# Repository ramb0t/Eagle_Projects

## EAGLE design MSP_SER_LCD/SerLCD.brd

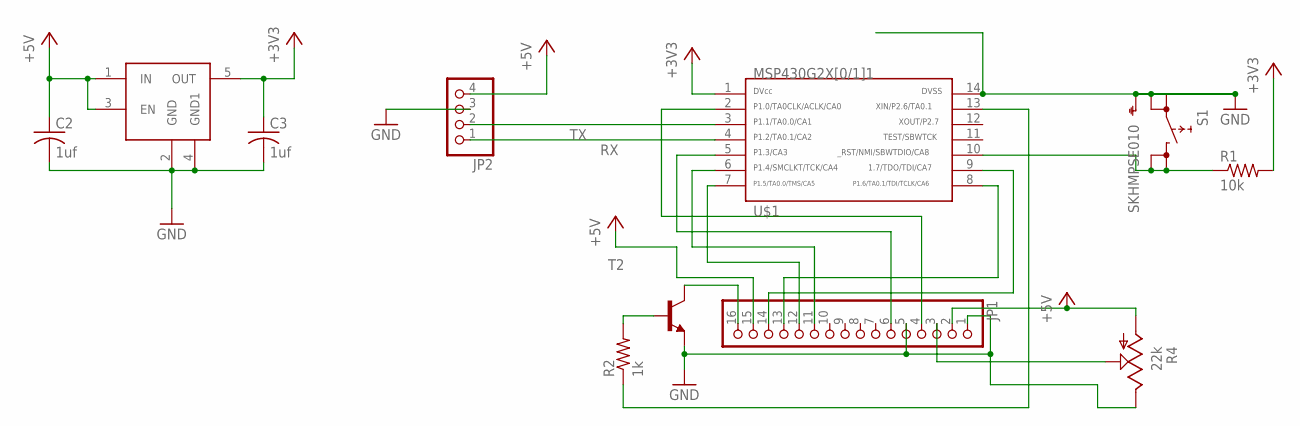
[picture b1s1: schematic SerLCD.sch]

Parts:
C2, C3: 1uf; C025-025X050
JP1: PINHD-1X16; 1X16
JP2: PINHD-1X4; 1X04
R1: 10k; 0207/10
R2: 1k; 0207/10
R4: 22k; CA6H
S1: SKHMPSE010; SKHMPXE010
T2: -NPN-TO92-EBC; TO92-EBC
U$1: G2X[0/1]1---N14; N14
U$2: TPS783XX; DBV-R-PDSO-G5

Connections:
+3V3: C3.1, R1.2, U$1.1, U$2.5 (OUT)
+5V: C2.1, JP1.2, JP1.15, JP2.4, R4.A, U$2.1 (IN), U$2.3 (EN)
GND: C2.2, C3.2, JP1.1, JP1.5, JP2.3, R4.E, S1.1 (1.1), S1.2 (1.2), S1.5 (SH), T2.E, U$1.14, U$2.2 (GND), U$2.4 (GND1)
unnamed: JP1.4, U$1.2
unnamed: JP1.6, U$1.5
unnamed: JP1.11, U$1.6
unnamed: JP1.12, U$1.7
unnamed: JP1.13, U$1.8
unnamed: JP1.14, U$1.9
unnamed: R1.1, S1.3 (2.1), S1.4 (2.2), U$1.10
unnamed: JP1.16, T2.C
unnamed: R2.2, T2.B
unnamed: R2.1, U$1.13
unnamed: JP1.3, R4.S
RX: JP2.1, U$1.4
TX: JP2.2, U$1.3

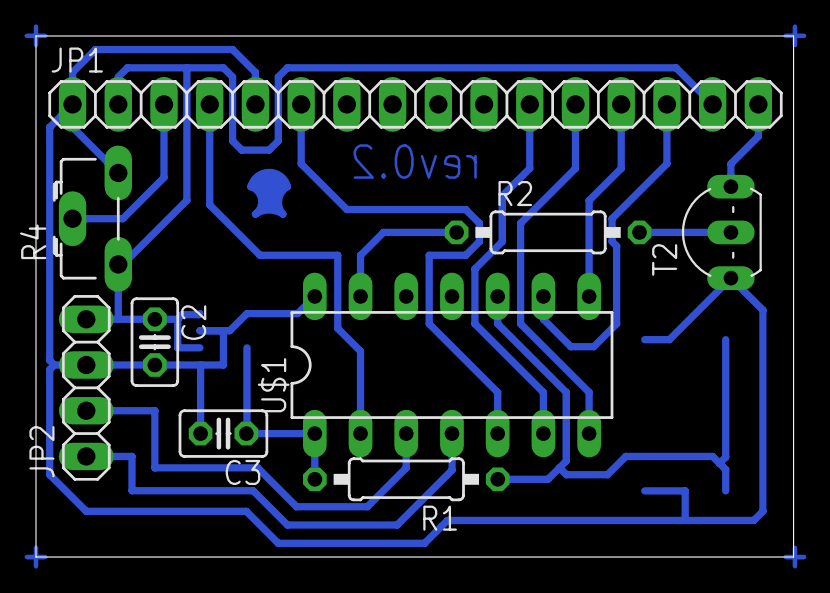
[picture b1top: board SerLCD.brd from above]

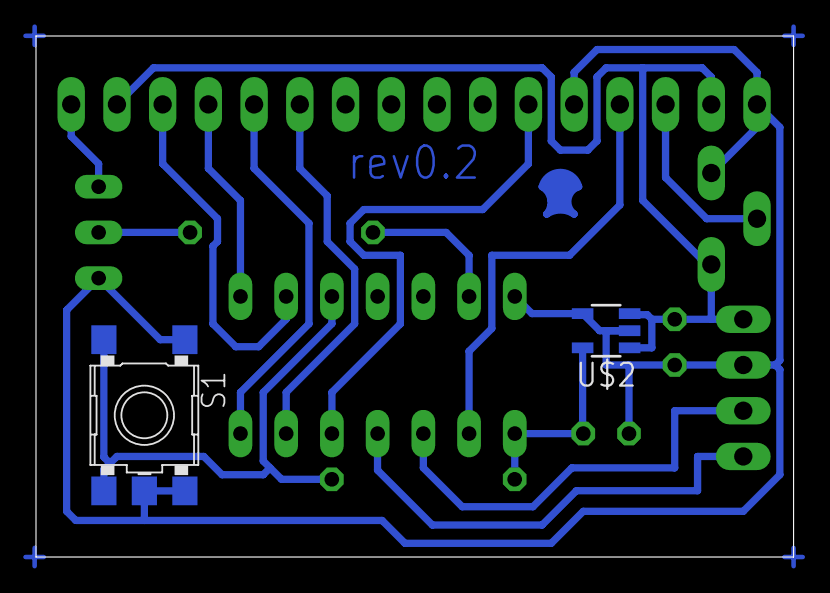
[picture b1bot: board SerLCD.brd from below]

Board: 2 copper layers, 42.1 x 28.9 mm, 11 parts (2 on the bottom side), 16 nets.

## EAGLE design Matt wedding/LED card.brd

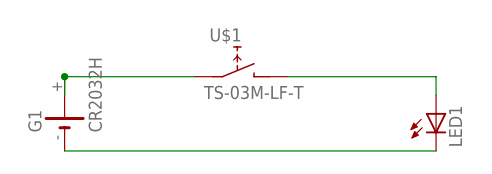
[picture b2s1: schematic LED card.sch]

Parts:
G1: CR2032H
LED1: LED5MM
U$1: TS-03M-LF-T

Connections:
unnamed: G1.+, G1.+@1 (+), U$1.P$1 (A1)
unnamed: LED1.A, U$1.P$2 (B)
unnamed: G1.-, LED1.K (C)

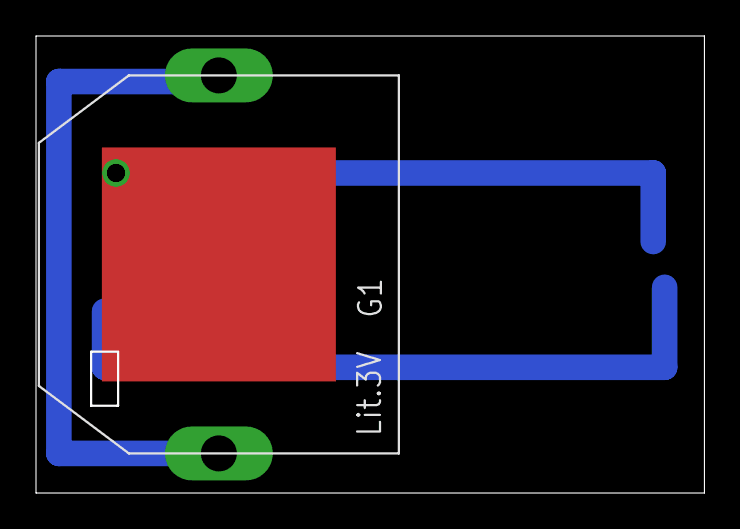
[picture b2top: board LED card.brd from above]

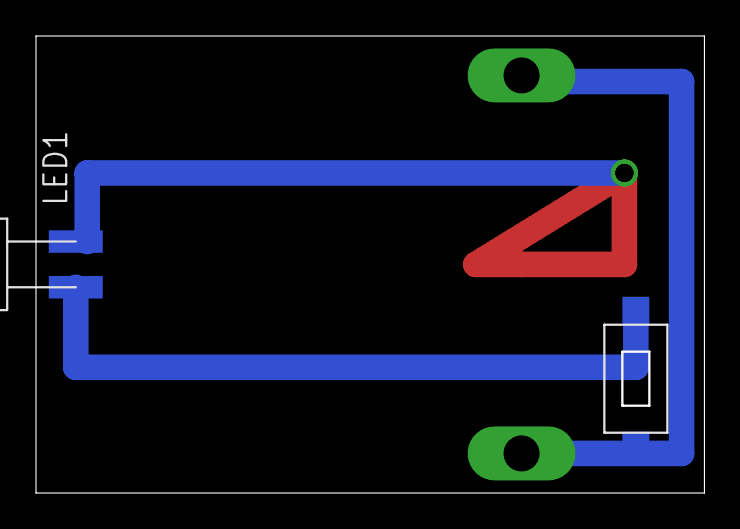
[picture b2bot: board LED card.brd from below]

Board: 2 copper layers, 37.1 x 25.4 mm, 3 parts (2 on the bottom side), 3 nets.

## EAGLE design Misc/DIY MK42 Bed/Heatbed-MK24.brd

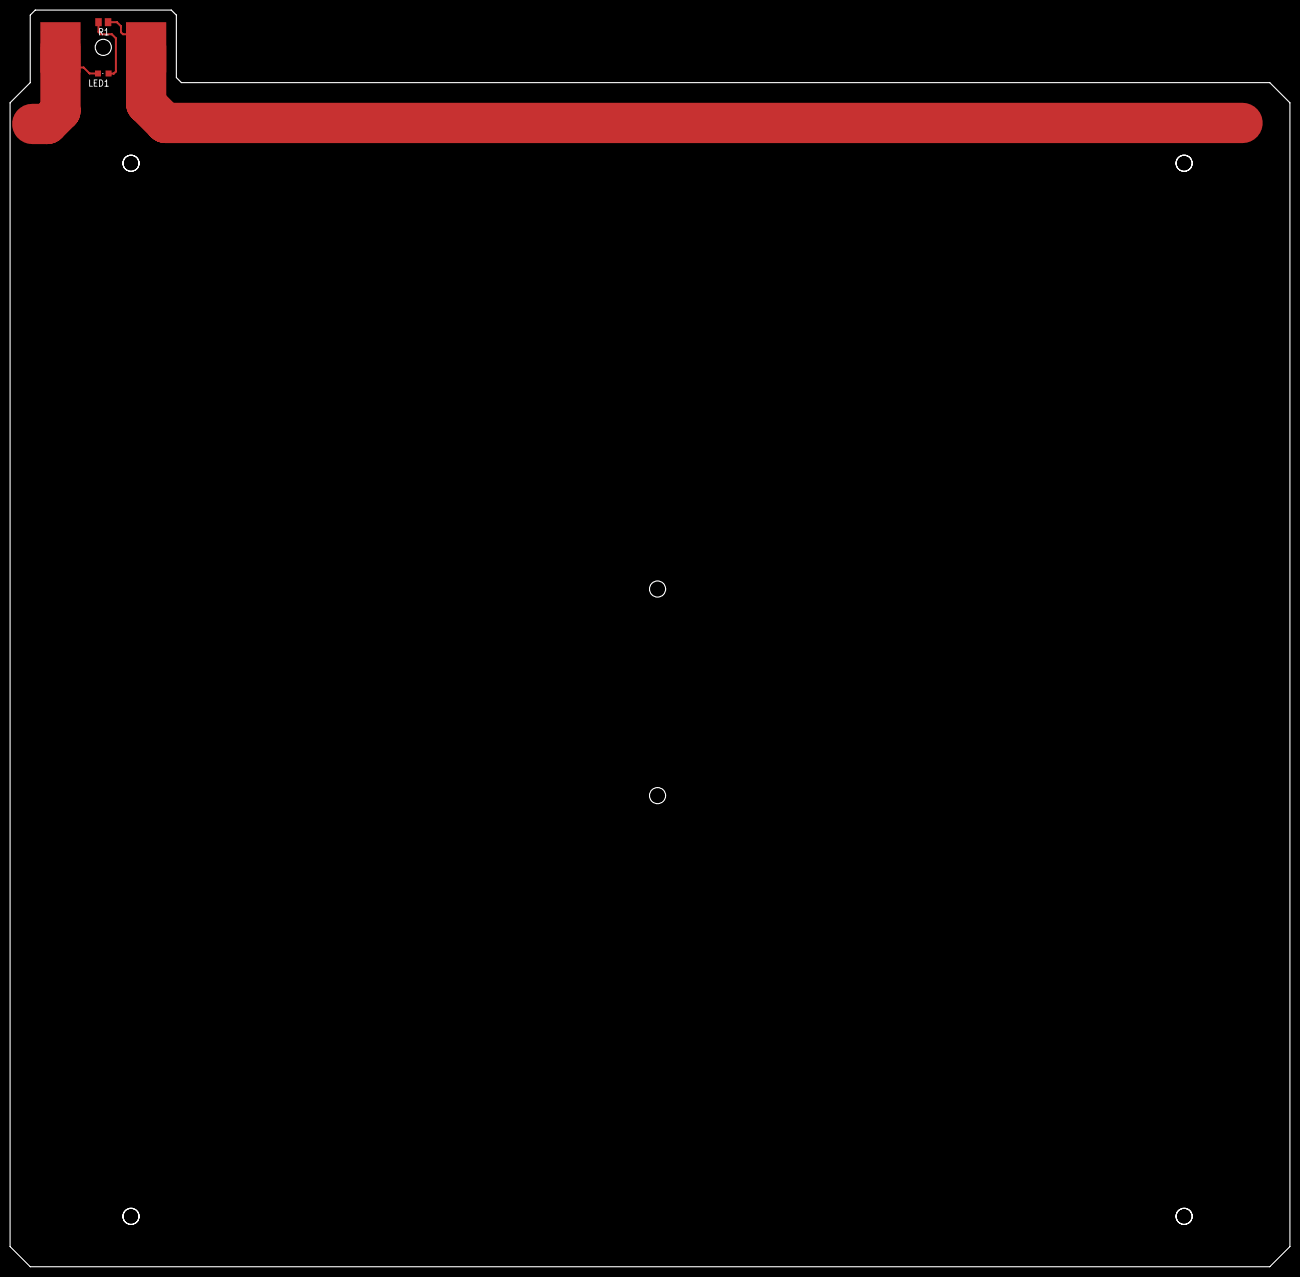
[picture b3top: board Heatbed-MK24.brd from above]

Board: 6 copper layers, 254.0 x 249.4 mm, 4 parts (0 on the bottom side), 2 nets.

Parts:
LED1: CHIPLED_0805
R1: 1k; M0805
U$1, U$2: FASTONSMD

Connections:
HEATER: LED1.C, R1.1, U$1.P$1, U$2.P$1
unnamed: LED1.A, R1.2

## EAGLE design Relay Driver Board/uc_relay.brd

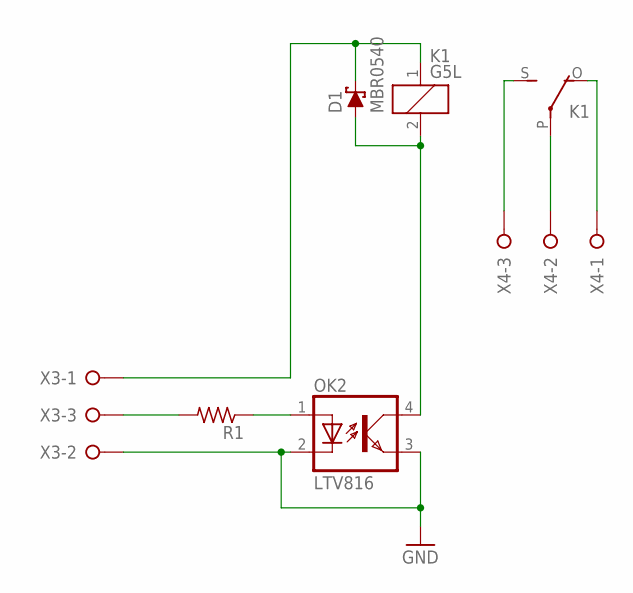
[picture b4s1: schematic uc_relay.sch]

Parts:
D1: MBR0540; SOD123
K1: G5L; G5LE
OK2: LTV816; DIL04
R1: R-US_R0805; R0805
X3, X4: W237-3E

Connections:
GND: OK2.2 (C), OK2.3 (EMIT), X3.2
unnamed: K1.S, X4.3
unnamed: K1.P, X4.2
unnamed: K1.O, X4.1
unnamed: R1.2, X3.3
unnamed: OK2.1 (A), R1.1
unnamed: D1.C, K1.1, X3.1
unnamed: D1.A, K1.2, OK2.4 (COL)

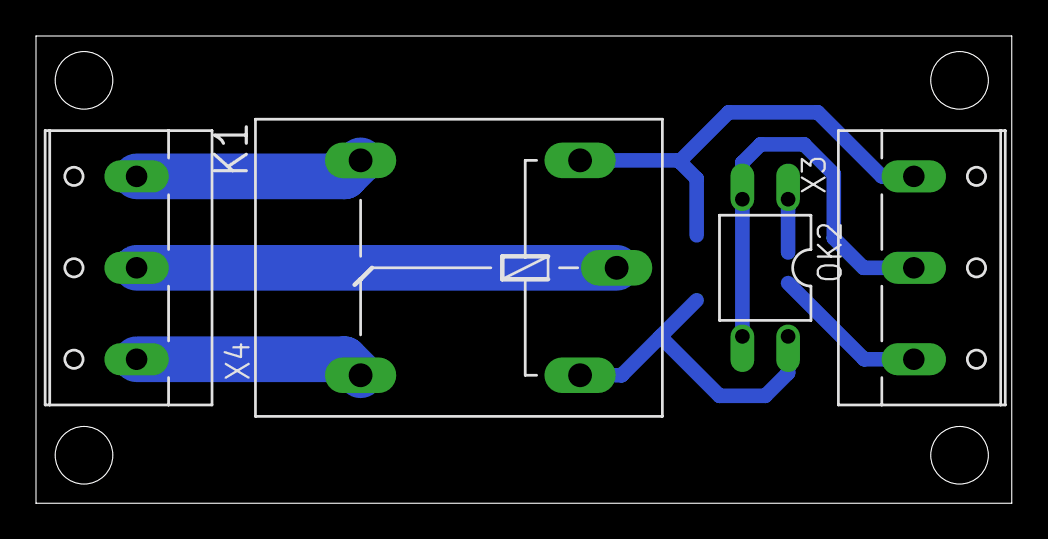
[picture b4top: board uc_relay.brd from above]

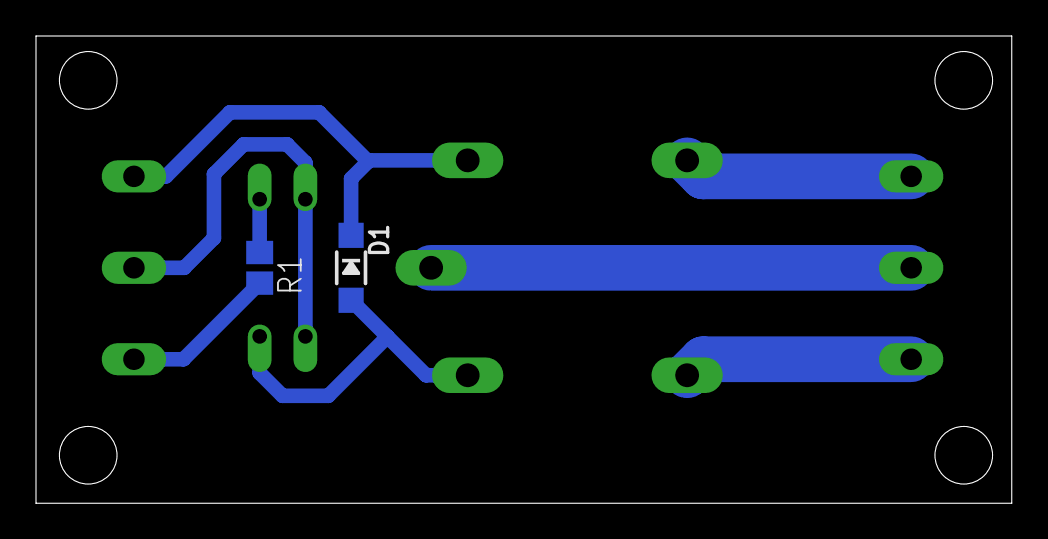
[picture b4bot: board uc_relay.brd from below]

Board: 2 copper layers, 54.2 x 26.0 mm, 6 parts (2 on the bottom side), 8 nets.

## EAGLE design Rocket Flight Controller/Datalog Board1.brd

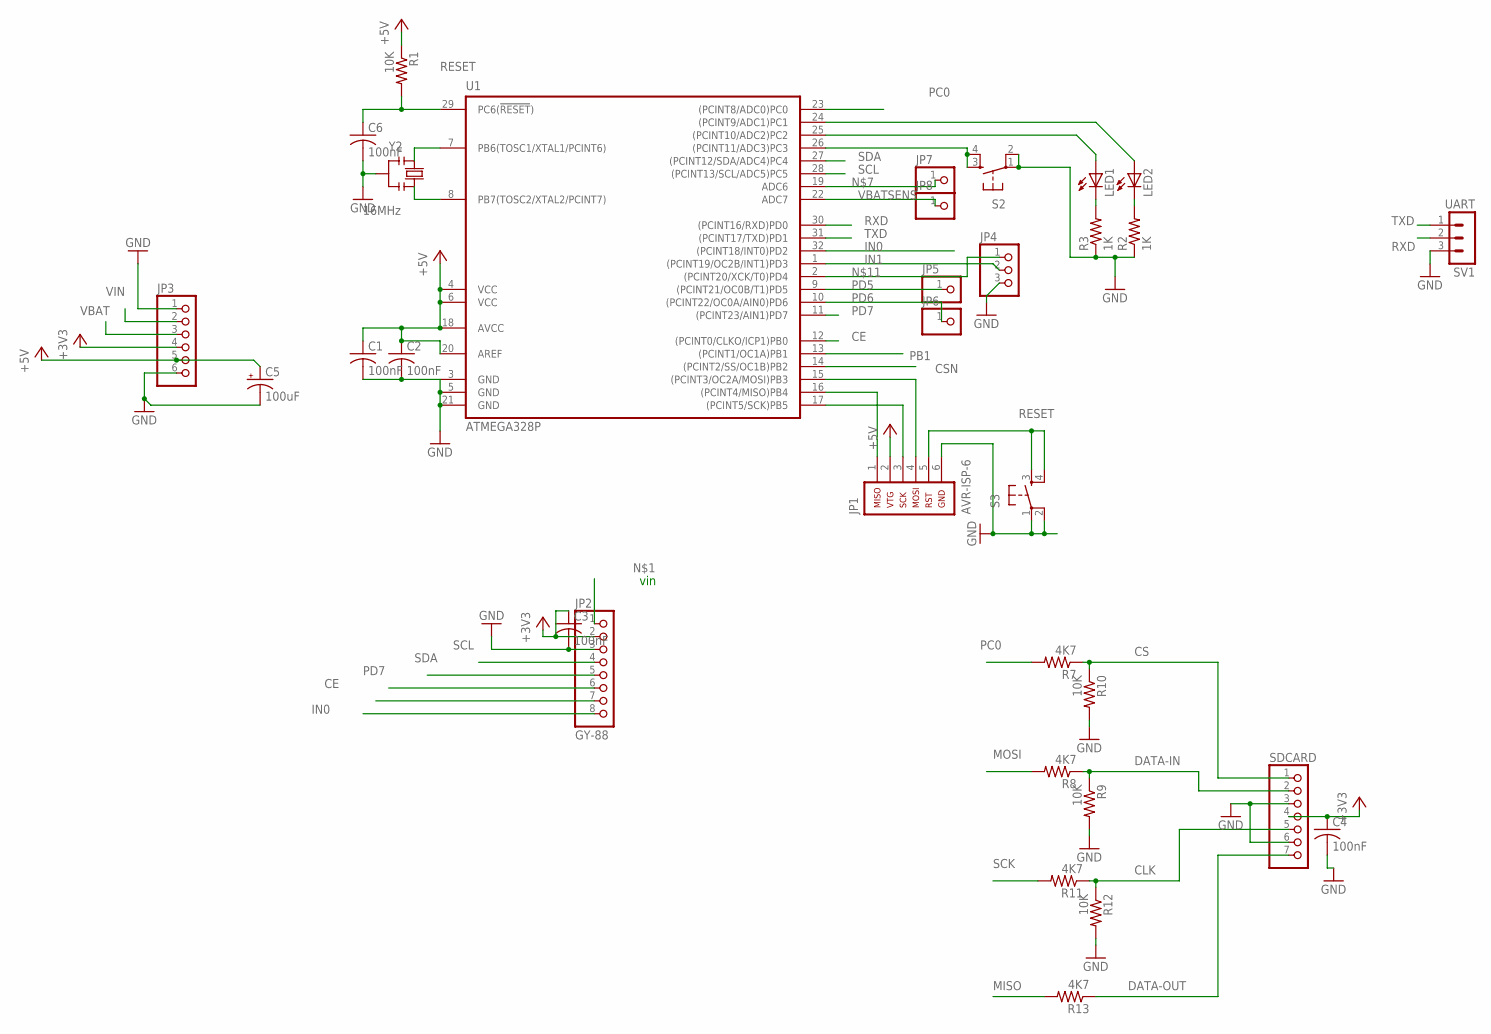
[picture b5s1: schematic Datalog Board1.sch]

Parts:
C1, C2, C3, C4, C6: 100nF; C0805K
C5: 100uF; PANASONIC_D
JP1: AVR-ISP-6
JP2: GY-88; 1X08
JP3: PINHD-1X6; 1X06
JP4: PINHD-1X3; 1X03
JP5, JP6, JP7, JP8: PINHD-1X1; 1X01
LED1, LED2: LEDCHIPLED_0805; CHIPLED_0805
R1, R9, R10, R12: 10K; R0805
R2, R3: 1K; R0805
R7, R8, R11, R13: 4K7; R0805
S2, S3: TAC_SWITCHSMD; TACTILE_SWITCH_SMD
SDCARD: PINHD-1X7; 1X07
SV1: UART; MA03-1
U1: ATMEGA328P; TQFP32A
Y2: 16MHz; RESONATOR

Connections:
+3V3: C3.1, C4.1, JP2.2, JP3.4, SDCARD.4
+5V: C1.1, C2.1, C5.+, JP1.2, JP3.5, R1.1, U1.4 (VCC), U1.6 (VCC), U1.18 (AVCC), U1.20 (AREF)
CE: JP2.7, U1.12 ((PCINT0/CLKO/ICP1)PB0)
CLK: R11.1, R12.1, SDCARD.5
CS: R7.1, R10.1, SDCARD.1
CSN: U1.14 ((PCINT2/SS/OC1B)PB2)
DATA-IN: R8.1, R9.1, SDCARD.2
DATA-OUT: R13.1, SDCARD.7
GND: C1.2, C2.2, C3.2, C4.2, C5.-, C6.2, JP1.6, JP2.3, JP3.1, JP3.6, JP4.3, R2.1, R3.1, R9.2, R10.2, R12.2, S2.1, S2.2, S3.1, S3.2, SDCARD.3, SDCARD.6, SV1.3, U1.3 (GND), U1.5 (GND), U1.21 (GND), Y2.2
IN0: JP2.8, U1.32 ((PCINT18/INT0)PD2)
IN1: JP4.2, U1.1 ((PCINT19/OC2B/INT1)PD3)
MISO: JP1.1, R13.2, U1.16 ((PCINT4/MISO)PB4)
MOSI: JP1.4, R8.2, U1.15 ((PCINT3/OC2A/MOSI)PB3)
unnamed: LED2.A, U1.24 ((PCINT9/ADC1)PC1)
unnamed: LED1.A, U1.25 ((PCINT10/ADC2)PC2)
unnamed: S2.3, S2.4, U1.26 ((PCINT11/ADC3)PC3)
unnamed: JP7.1, U1.19 (ADC6)
unnamed: U1.8 (PB7(TOSC2/XTAL2/PCINT7)), Y2.3
unnamed: U1.7 (PB6(TOSC1/XTAL1/PCINT6)), Y2.1
unnamed: JP4.1, U1.2 ((PCINT20/XCK/T0)PD4)
unnamed: LED2.C, R2.2
unnamed: LED1.C, R3.2
PB1: U1.13 ((PCINT1/OC1A)PB1)
PC0: R7.2, U1.23 ((PCINT8/ADC0)PC0)
PD5: JP5.1, U1.9 ((PCINT21/OC0B/T1)PD5)
PD6: JP6.1, U1.10 ((PCINT22/OC0A/AIN0)PD6)
PD7: JP2.6, U1.11 ((PCINT23/AIN1)PD7)
RESET: C6.1, JP1.5, R1.2, S3.3, S3.4, U1.29 (PC6(!RESET!))
RXD: SV1.2, U1.30 ((PCINT16/RXD)PD0)
SCK: JP1.3, R11.2, U1.17 ((PCINT5/SCK)PB5)
SCL: JP2.4, U1.28 ((PCINT13/SCL/ADC5)PC5)
SDA: JP2.5, U1.27 ((PCINT12/SDA/ADC4)PC4)
TXD: SV1.1, U1.31 ((PCINT17/TXD)PD1)
VBAT: JP3.3
VBATSENS: JP8.1, U1.22 (ADC7)
VIN: JP3.2

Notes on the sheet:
vin

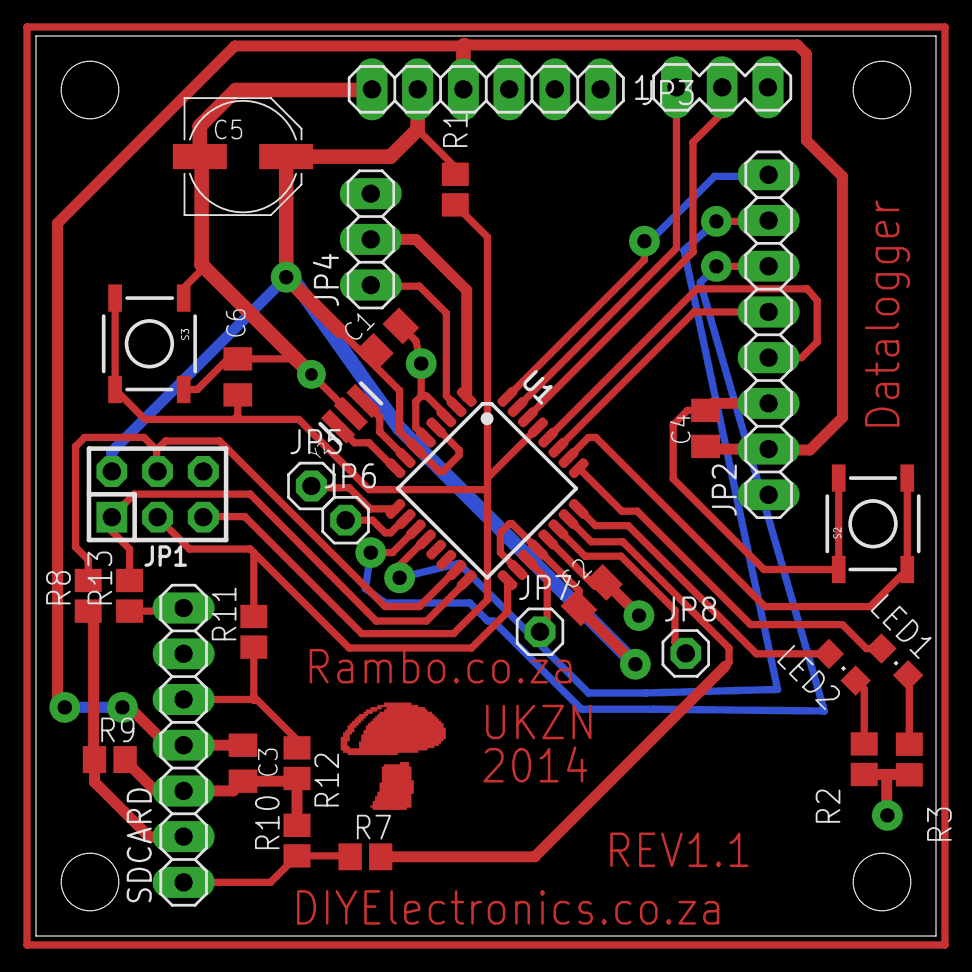
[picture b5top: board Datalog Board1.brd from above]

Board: 2 copper layers, 50.0 x 50.0 mm, 32 parts (0 on the bottom side), 32 nets.

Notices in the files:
parts and their libraries:
atmel-avr: Copyright (C) 2008, Bob Starr
SparkFun: Licensing: CC v3.0 Share-Alike You are welcome to use this library for commercial purposes.
